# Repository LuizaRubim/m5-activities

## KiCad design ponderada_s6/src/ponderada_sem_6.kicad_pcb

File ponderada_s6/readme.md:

# Fabricação PCB de identificado de cores

## Introdução
O projeto desse repositório é uma prototipação para a fabricação de uma PCB para identificação de cores com um sensor de proximidade e RGB e três leds para reprodução das cores, além de um buzzer para alertas. Essa placa também possui um conector para o microcontrolador Raspberry Pico W, que será o responsável por controlar o sistema. O projeto foi desenvolvido no KiCad e os arquivos gerber estão disponíveis para download.

## Estrutura de arquivos

Para encontrar os seguintes arquivos, basta acessar a pasta src ou clicar nos link abaixo:

#### Projeto completo: [ponderada_sem_6.kicad_pro](https://github.com/LuizaRubim/m5-activities/blob/main/ponderada_s6/src/ponderada_sem_6.kicad_pro)
<br>
Esse arquivo dá acesso completo aoa arquivos do projeto e pode ser aberto no KiCad, cao tenha instalado na sua máquina.

#### Desenho esquemático: [ponderada_sem_6.kicad_sch](https://github.com/LuizaRubim/m5-activities/blob/main/ponderada_s6/src/ponderada_sem_6.kicad_sch)
<br>
Esse arquivo contém o desenho esquemático e é a partir dele que se pode ter uma visão de quais componentes estão presentes na placa, além de poder ver as especificações de cada componente.

#### PCB: [ponderada_sem_6.kicad_pcb](https://github.com/LuizaRubim/m5-activities/blob/main/ponderada_s6/src/ponderada_sem_6.kicad_pcb)

Esse arquivo contém o desenho da placa de circuito impresso e é a partir dele que se pode ter uma visão de como os componentes estão dispostos na placa, as ligações que serão impressas e o tamanho da placa.

#### Gerber: [arquivos gerber](https://github.com/LuizaRubim/m5-activities/blob/main/ponderada_s6/src/arquivos_gerbers)

Essa pasta contém os arquivos gerber, que são os arquivos que serão enviados para a fábrica de PCBs para que a placa seja impressa.

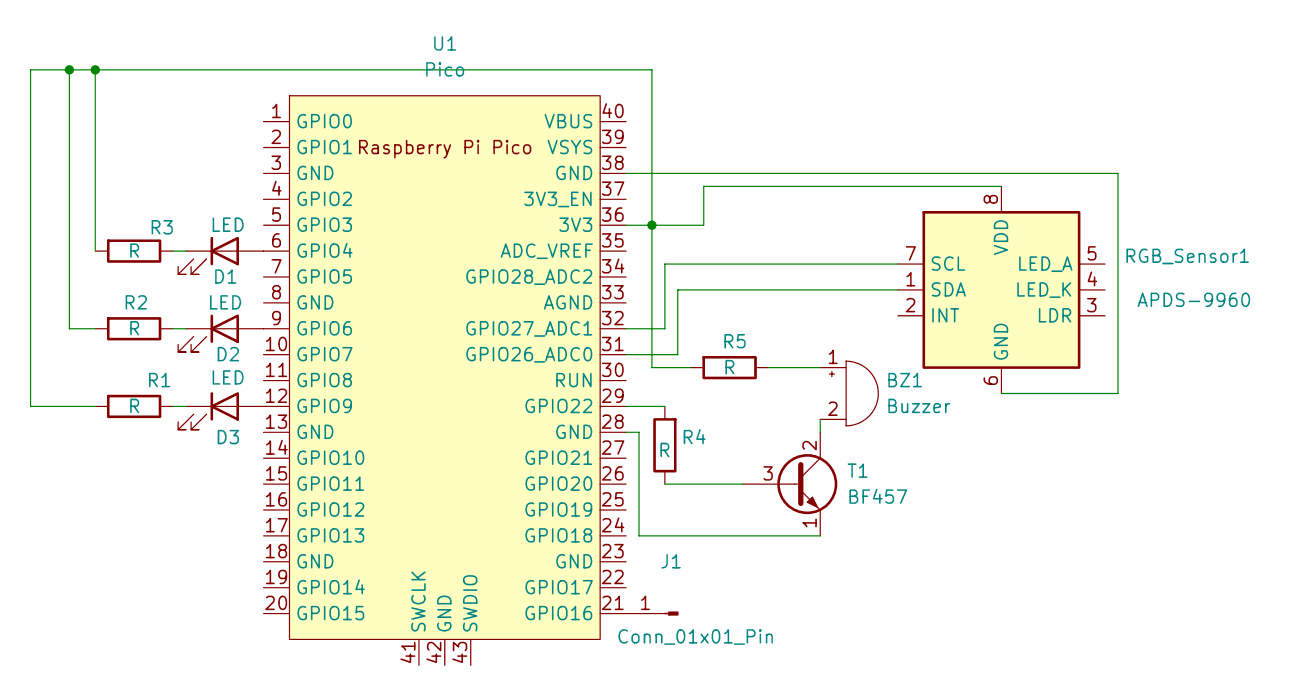
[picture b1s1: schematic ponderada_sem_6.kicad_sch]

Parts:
BZ1: Buzzer; MagneticBuzzer_ProSignal_ABI-009-RC
D1, D2, D3: LED; LED_D3.0mm
J1: Conn_01x01_Pin; PinHeader_1x01_P1.00mm_Vertical
R1, R2, R3, R4, R5: R; R_Axial_DIN0204_L3.6mm_D1.6mm_P7.62mm_Horizontal
RGB_Sensor1: APDS-9960; Avago_APDS-9960
T1: BF457; TO-92_Inline
U1: Pico; RPi_Pico_SMD_TH

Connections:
unnamed: BZ1.1 (+), R5.1
unnamed: BZ1.2 (-), T1.2 (C)
unnamed: D1.2 (A), U1.6 (GPIO4)
unnamed: D1.1 (K), R3.1
unnamed: D2.2 (A), U1.9 (GPIO6)
unnamed: D2.1 (K), R2.1
unnamed: D3.2 (A), U1.12 (GPIO9)
unnamed: D3.1 (K), R1.1
unnamed: J1.1, U1.21 (GPIO16)
unnamed: RGB_Sensor1.6 (GND), U1.38 (GND)
unnamed: RGB_Sensor1.7 (SCL), U1.32 (GPIO27_ADC1)
unnamed: RGB_Sensor1.1 (SDA), U1.31 (GPIO26_ADC0)
unnamed: R1.2, R2.2, R3.2, R5.2, RGB_Sensor1.8 (VDD), U1.36 (3V3)
unnamed: R4.1, T1.3 (B)
unnamed: T1.1 (E), U1.28 (GND)
unnamed: R4.2, U1.29 (GPIO22)

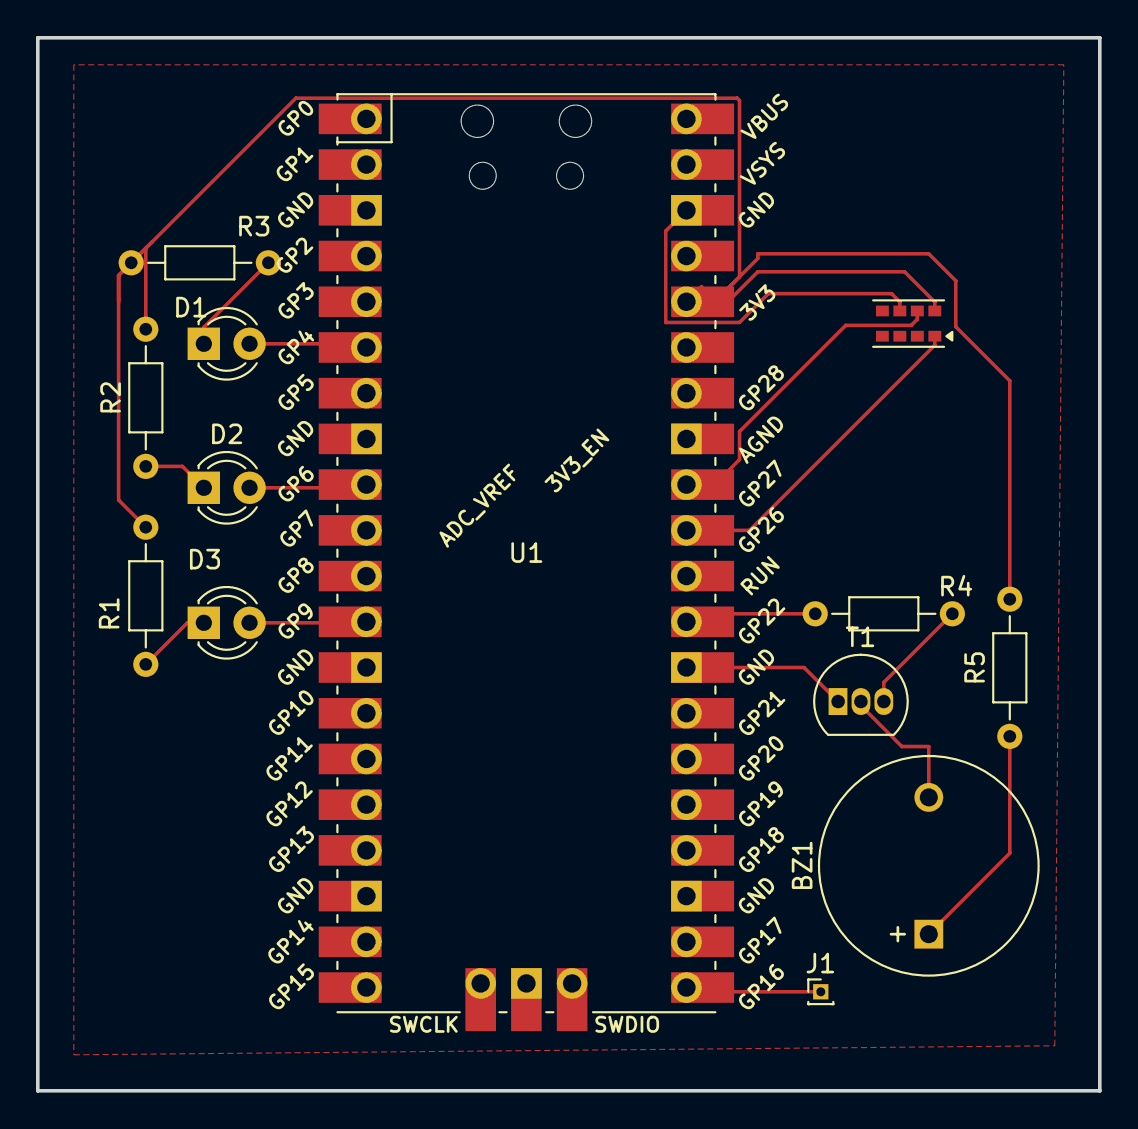
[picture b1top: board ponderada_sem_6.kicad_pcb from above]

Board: 2 copper layers, 59.0 x 58.5 mm, 13 parts (0 on the bottom side), 16 nets.

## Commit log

2024-02-13 commit inicial
2024-02-19 ajustes yaml do deploy
2024-02-19 página sobre mim
2024-02-19 página inicial
2024-02-19 removendo arquivos não utilizados + ajustes no blog
2024-03-01 atividade ponderada semana 3
2024-04-01 ponderada_sem_6
2024-04-01 completando readme
2024-04-05 ponderada semana 7
2024-04-05 add readme e requirements
2024-04-05 deletando pycache
2024-04-05 ajuste autorizacao movimentacao + att readme
2024-04-05 add vídeo e ajustes finais ponderada s7
